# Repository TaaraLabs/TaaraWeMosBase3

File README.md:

TaaraWeMosBase 3
================

Triple base board for popular WeMos D1 (ESP8266) and WeMos S2 (ESP32) microcontroller boards and shields.

[WebSite](https://taaralabs.eu/wb3)

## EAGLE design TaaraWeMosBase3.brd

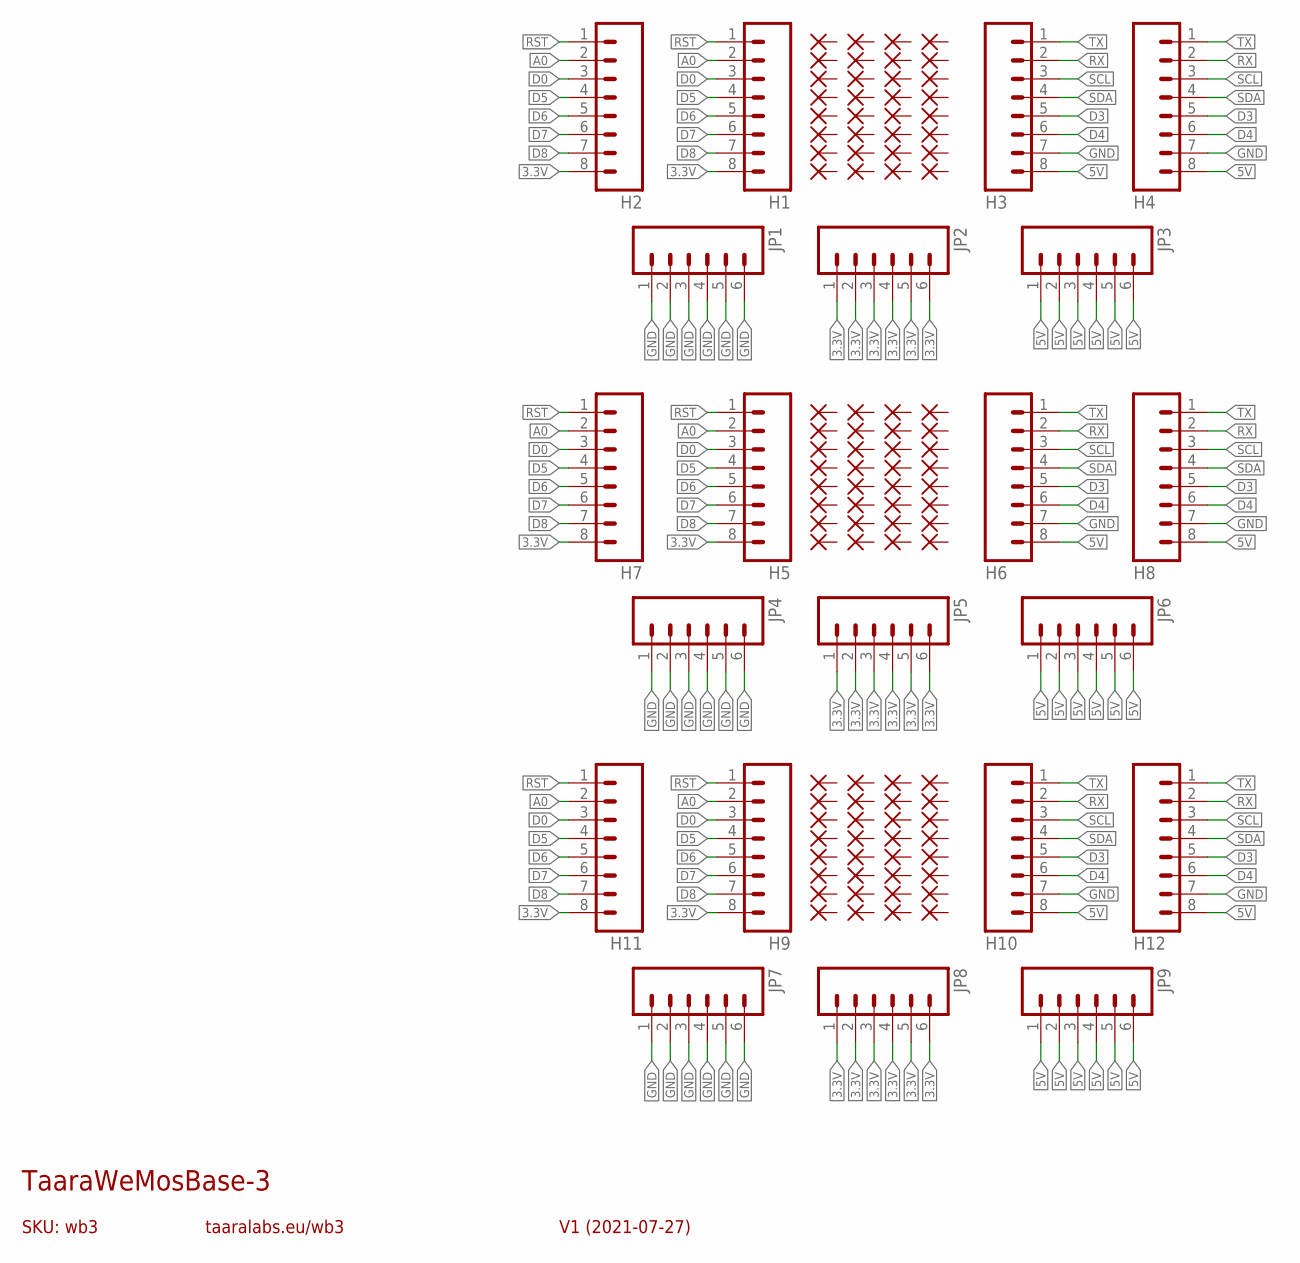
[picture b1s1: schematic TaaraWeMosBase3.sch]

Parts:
H1, H2, H3, H4, H5, H6, H7, H8, H9, H10, H11, H12: M08; 1X08
JP1, JP2, JP3, JP4, JP5, JP6, JP7, JP8, JP9: M06SIP; 1X06
PAD1, PAD2, PAD3, PAD4, PAD5, PAD6, PAD7, PAD8, PAD9, PAD10, PAD11, PAD12, PAD13, PAD14, PAD15, PAD16, PAD17, PAD18, PAD19, PAD20, PAD21, PAD22, PAD23, PAD24, PAD25, PAD26, PAD27, PAD28, PAD29, PAD30, PAD31, PAD32, PAD33, PAD34, PAD35, PAD36, PAD37, PAD38, PAD39, PAD40, PAD41, PAD42, PAD43, PAD44, PAD45, PAD46, PAD47, PAD48, PAD49, PAD50, PAD51, PAD52, PAD53, PAD54, PAD55, PAD56, PAD57, PAD58, PAD59, PAD60, PAD61, PAD62, PAD63, PAD64, PAD65, PAD66, PAD67, PAD68, PAD69, PAD70, PAD71, PAD72, PAD73, PAD74, PAD75, PAD76, PAD77, PAD78, PAD79, PAD80, PAD81, PAD82, PAD83, PAD84, PAD85, PAD86, PAD87, PAD88, PAD89, PAD90, PAD91, PAD92, PAD93, PAD94, PAD95, PAD96: 1,6/0,8

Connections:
3.3V: H1.8, H2.8, H5.8, H7.8, H9.8, H11.8, JP2.1, JP2.2, JP2.3, JP2.4, JP2.5, JP2.6, JP5.1, JP5.2, JP5.3, JP5.4, JP5.5, JP5.6, JP8.1, JP8.2, JP8.3, JP8.4, JP8.5, JP8.6
5V: H3.8, H4.8, H6.8, H8.8, H10.8, H12.8, JP3.1, JP3.2, JP3.3, JP3.4, JP3.5, JP3.6, JP6.1, JP6.2, JP6.3, JP6.4, JP6.5, JP6.6, JP9.1, JP9.2, JP9.3, JP9.4, JP9.5, JP9.6
A0: H1.2, H2.2, H5.2, H7.2, H9.2, H11.2
D0: H1.3, H2.3, H5.3, H7.3, H9.3, H11.3
D3: H3.5, H4.5, H6.5, H8.5, H10.5, H12.5
D4: H3.6, H4.6, H6.6, H8.6, H10.6, H12.6
D5: H1.4, H2.4, H5.4, H7.4, H9.4, H11.4
D6: H1.5, H2.5, H5.5, H7.5, H9.5, H11.5
D7: H1.6, H2.6, H5.6, H7.6, H9.6, H11.6
D8: H1.7, H2.7, H5.7, H7.7, H9.7, H11.7
GND: H3.7, H4.7, H6.7, H8.7, H10.7, H12.7, JP1.1, JP1.2, JP1.3, JP1.4, JP1.5, JP1.6, JP4.1, JP4.2, JP4.3, JP4.4, JP4.5, JP4.6, JP7.1, JP7.2, JP7.3, JP7.4, JP7.5, JP7.6
RST: H1.1, H2.1, H5.1, H7.1, H9.1, H11.1
RX: H3.2, H4.2, H6.2, H8.2, H10.2, H12.2
SCL: H3.3, H4.3, H6.3, H8.3, H10.3, H12.3
SDA: H3.4, H4.4, H6.4, H8.4, H10.4, H12.4
TX: H3.1, H4.1, H6.1, H8.1, H10.1, H12.1

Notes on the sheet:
SKU: wb3
TaaraWeMosBase-3
V1 (2021-07-27)
taaralabs.eu/wb3

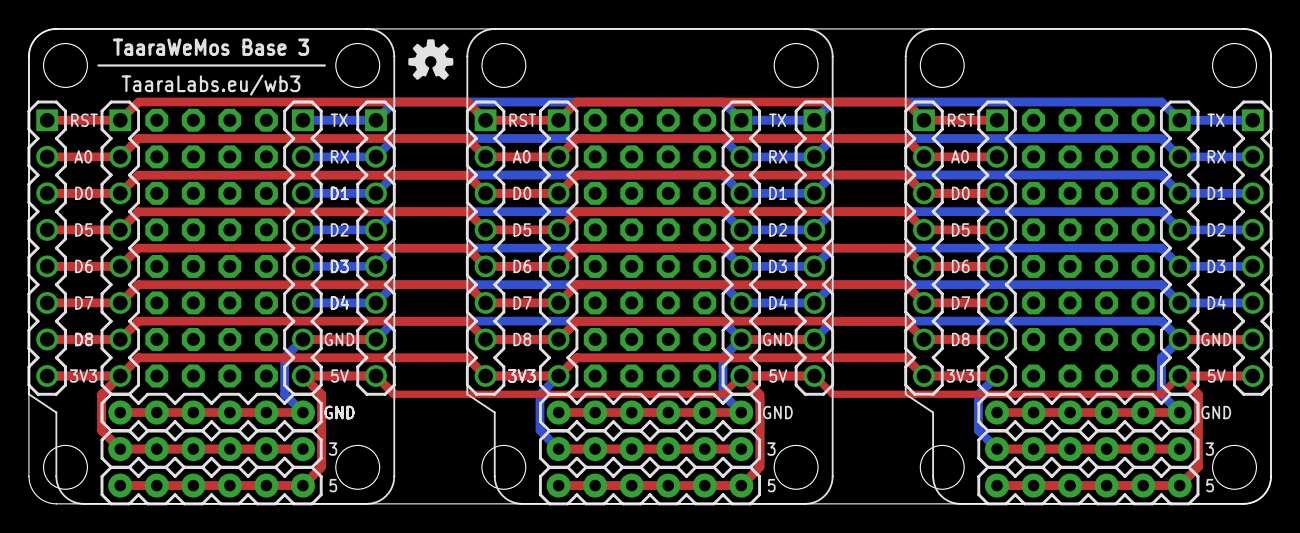
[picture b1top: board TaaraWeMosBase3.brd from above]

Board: 2 copper layers, 86.4 x 33.0 mm, 119 parts (1 on the bottom side), 16 nets.

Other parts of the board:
U$1, U$2: OSHW-LOGO-S

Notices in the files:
parts and their libraries:
freetronics-original: Licensing: CC v3.0 Share-Alike You are welcome to use this library for commercial purposes.
